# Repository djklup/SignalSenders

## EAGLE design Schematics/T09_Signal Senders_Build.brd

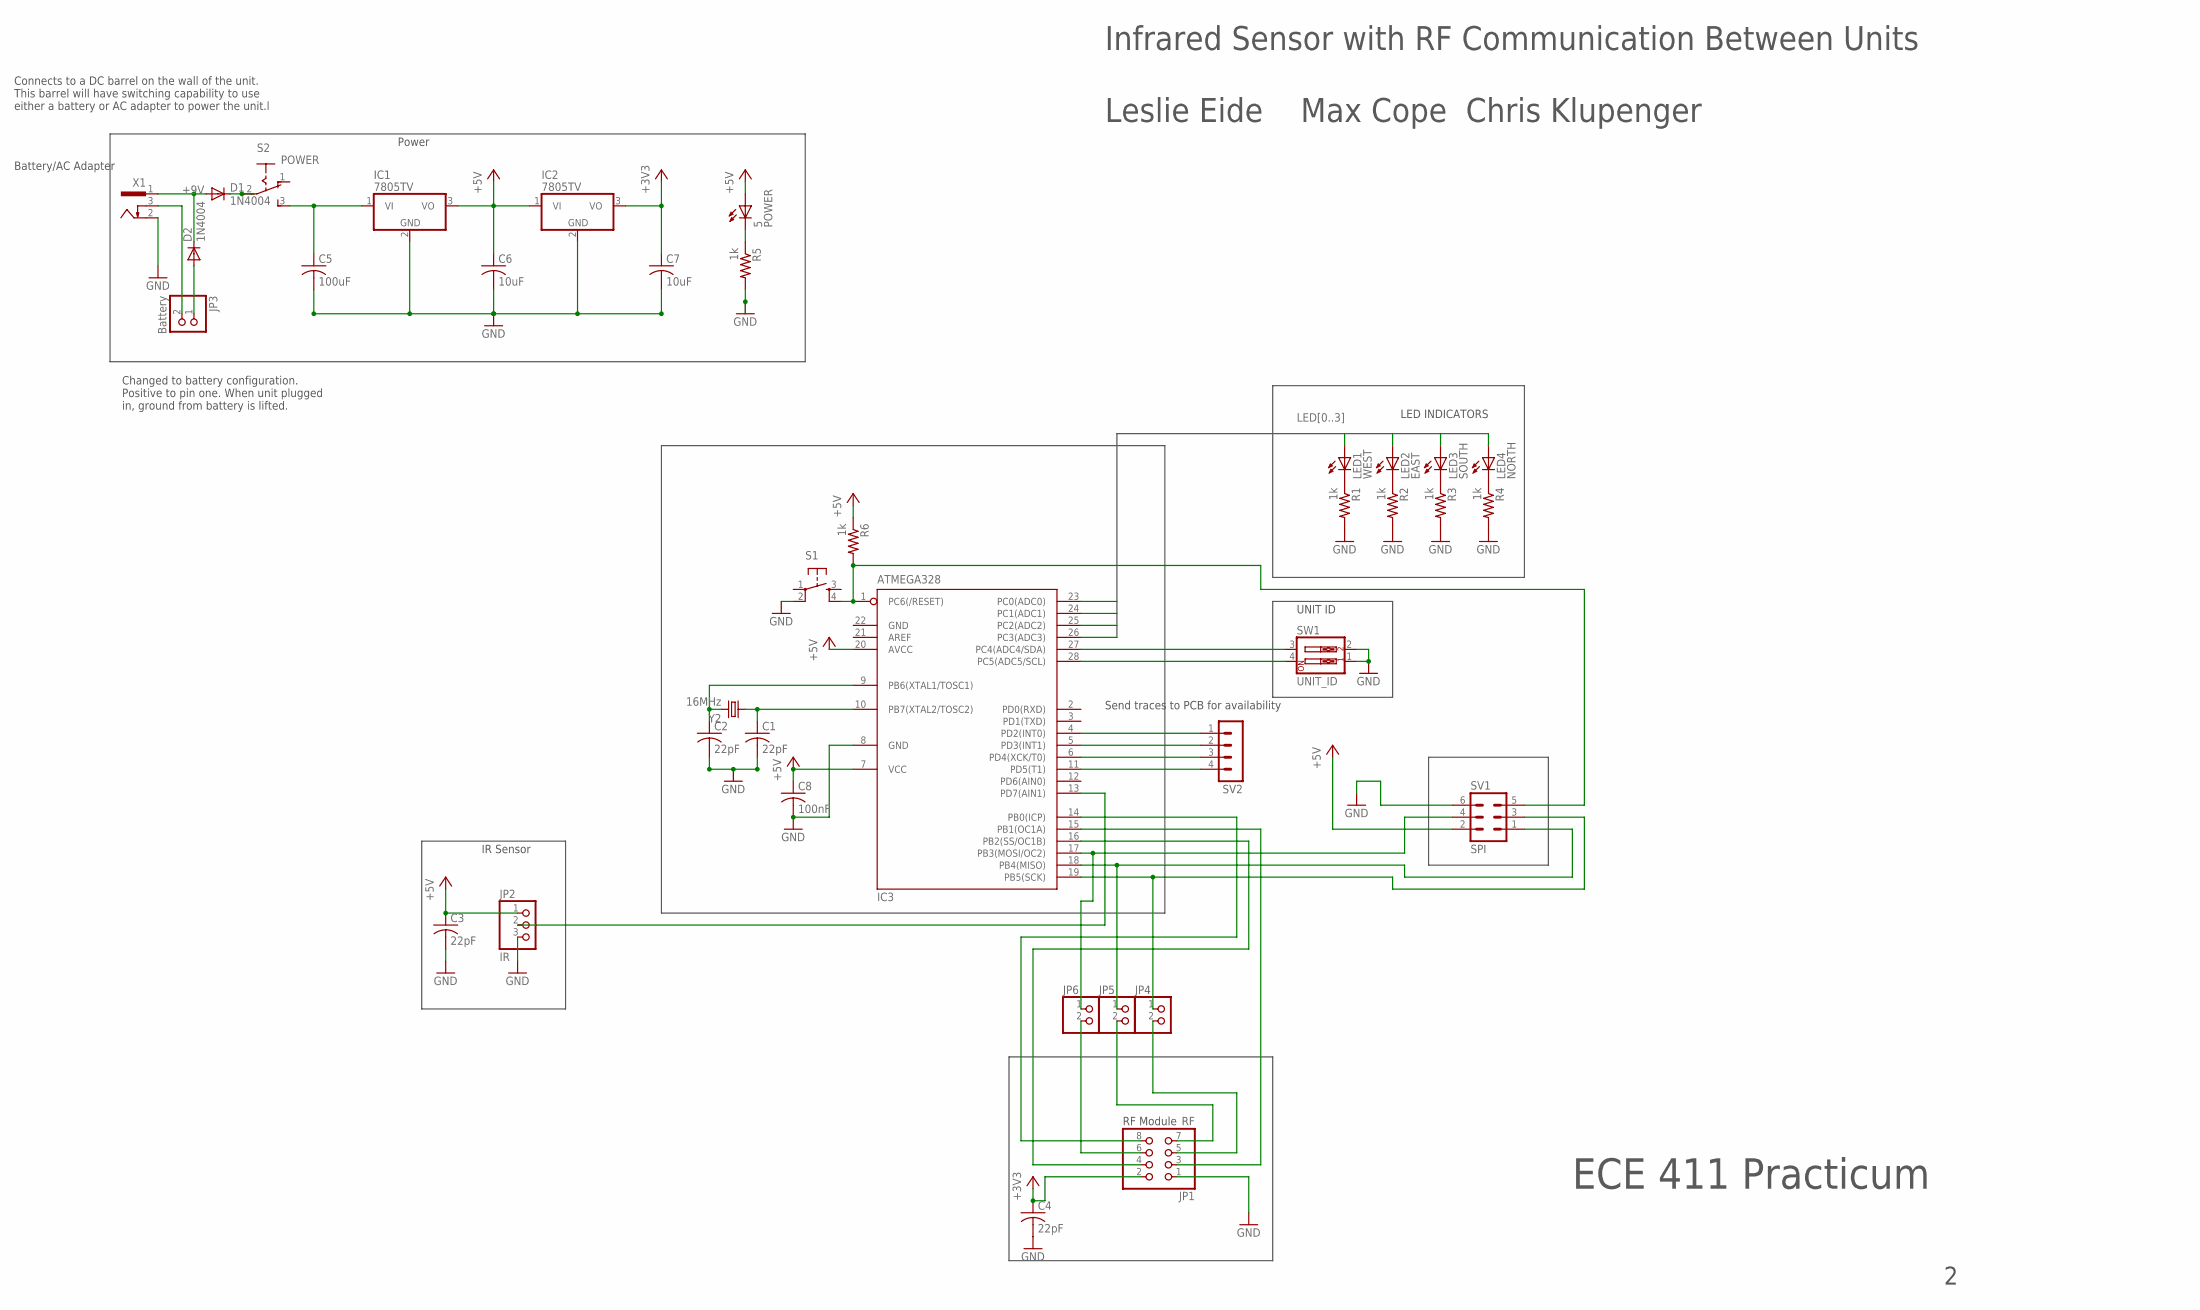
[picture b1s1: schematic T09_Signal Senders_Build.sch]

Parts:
5: POWER; LED3MM
C1, C2, C3, C4: 22pF; C0805
C5: 100uF; C050-075X075
C6, C7: 10uF; C0805
C8: 100nF; C0805
D1, D2: 1N4004; DO41-10
IC1, IC2: 7805TV; TO220V
IC3: ATMEGA328; DIL28-3
JP1: RF; 2X04
JP2: IR; 1X03
JP3: Battery; 1X02
JP4, JP5, JP6: 1X02
LED1: WEST; LED3MM
LED2: EAST; LED3MM
LED3: SOUTH; LED3MM
LED4: NORTH; LED3MM
R1, R2, R3, R4, R5, R6: 1k; M0805
S1: TACTILE-PTH
S2: POWER; M251
SV1: SPI; MA03-2
SV2: MA04-1
SW1: UNIT_ID; EDG-02
X1: 733980-62
Y2: 16MHz; HC49US

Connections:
+3V3: C4.1, C7.1, IC2.3 (VO), JP1.2
+5V: 5.A, C3.1, C6.1, C8.1, IC1.3 (VO), IC2.1 (VI), IC3.7 (VCC), IC3.20 (AVCC), JP2.1, R6.1, SV1.2
+9V: D1.A, D2.C, X1.1
GND: C1.2, C2.2, C3.2, C4.2, C5.2, C6.2, C7.2, C8.2, IC1.2 (GND), IC2.2 (GND), IC3.8 (GND), IC3.22 (GND), JP1.1, JP2.3, R1.2, R2.2, R3.2, R4.2, R5.2, S1.2, SV1.6, SW1.1, SW1.2, X1.2
LED0: IC3.23 (PC0(ADC0)), LED1.A
LED1: IC3.24 (PC1(ADC1)), LED2.A
LED2: IC3.25 (PC2(ADC2)), LED3.A
LED3: IC3.26 (PC3(ADC3)), LED4.A
unnamed: IC3.1 (PC6(/RESET)), R6.2, S1.4, SV1.5
unnamed: C1.1, IC3.10 (PB7(XTAL2/TOSC2)), Y2.1
unnamed: C2.1, IC3.9 (PB6(XTAL1/TOSC1)), Y2.2
unnamed: IC3.13 (PD7(AIN1)), JP2.2
unnamed: LED1.K (C), R1.1
unnamed: LED2.K (C), R2.1
unnamed: LED3.K (C), R3.1
unnamed: LED4.K (C), R4.1
unnamed: IC3.27 (PC4(ADC4/SDA)), SW1.3
unnamed: IC3.28 (PC5(ADC5/SCL)), SW1.4
unnamed: IC3.4 (PD2(INT0)), SV2.1
unnamed: IC3.5 (PD3(INT1)), SV2.2
unnamed: D2.A, JP3.1
unnamed: JP3.2, X1.3
unnamed: IC3.6 (PD4(XCK/T0)), SV2.3
unnamed: IC3.11 (PD5(T1)), SV2.4
unnamed: 5.K (C), R5.1
unnamed: C5.1, IC1.1 (VI), S2.3 (S)
unnamed: D1.C, S2.2
unnamed: IC3.18 (PB4(MISO)), JP5.1, SV1.1
unnamed: IC3.17 (PB3(MOSI/OC2)), JP6.1, SV1.4
unnamed: IC3.19 (PB5(SCK)), JP4.1, SV1.3
unnamed: IC3.16 (PB2(SS/OC1B)), JP1.4
unnamed: IC3.14 (PB0(ICP)), JP1.8
unnamed: IC3.15 (PB1(OC1A)), JP1.3
unnamed: JP1.6, JP6.2
unnamed: JP1.7, JP5.2
unnamed: JP1.5, JP4.2

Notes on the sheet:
LED INDICATORS
RF Module
IR Sensor
UNIT ID
Power
Infrared Sensor with RF Communication Between Units Leslie Eide Max Cope Chris Klupenger
Battery/AC Adapter
ECE 411 Practicum
Send traces to PCB for availability
Connects to a DC barrel on the wall of the unit. This barrel will have switching capability to use either a battery or AC adapter to power the unit.l
Changed to battery configuration. Positive to pin one. When unit plugged in, ground from battery is lifted.

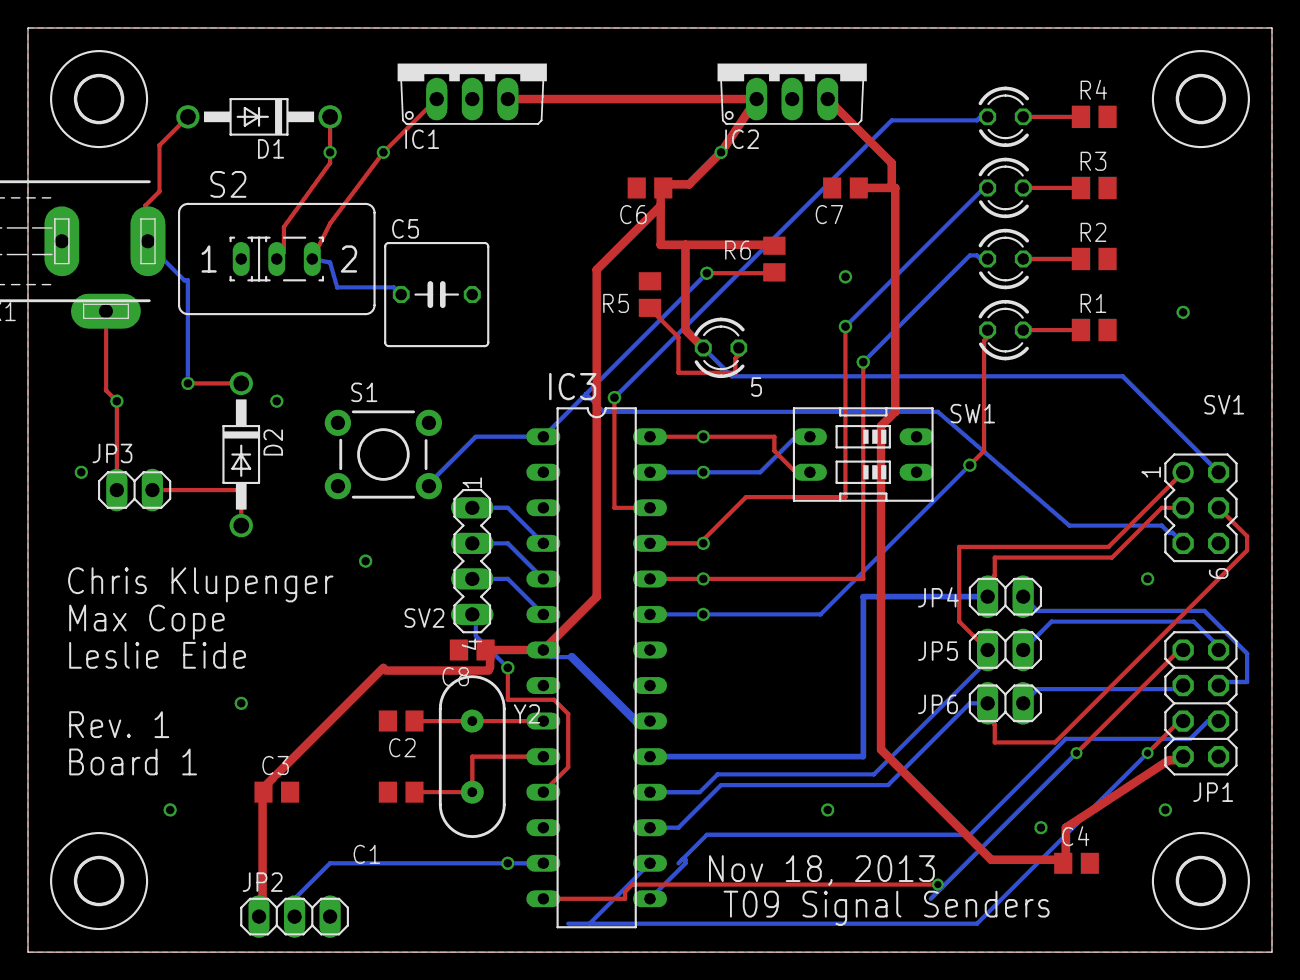
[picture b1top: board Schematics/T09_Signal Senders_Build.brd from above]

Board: 2 copper layers, 88.9 x 66.0 mm, 41 parts (0 on the bottom side), 36 nets.

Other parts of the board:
U$1, U$2, U$3, U$4: 3,2

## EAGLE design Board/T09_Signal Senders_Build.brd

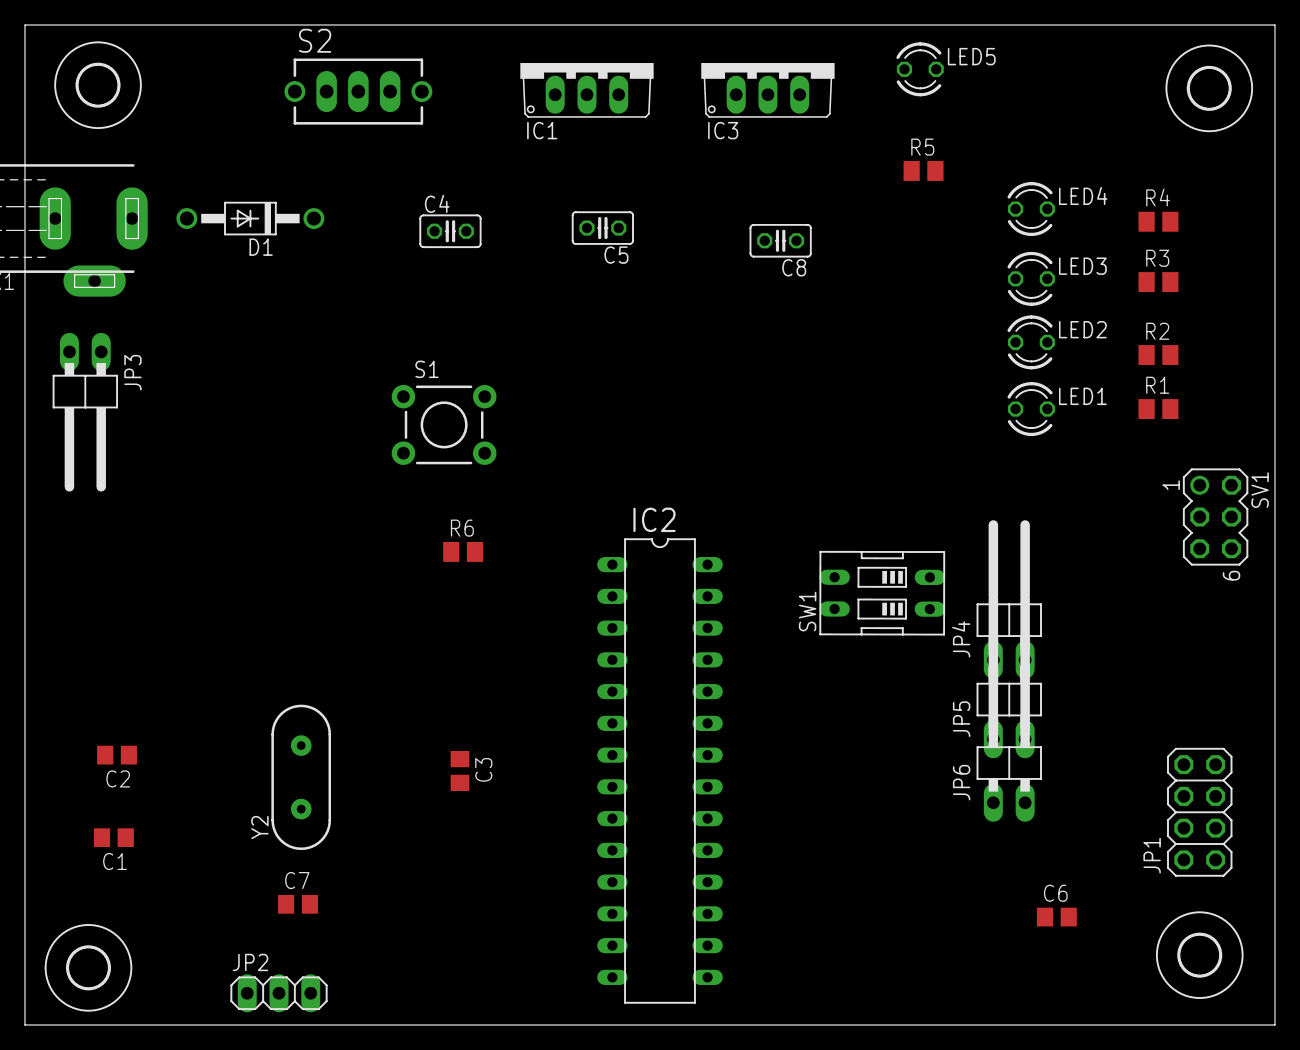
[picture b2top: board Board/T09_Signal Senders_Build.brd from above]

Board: 2 copper layers, 100.0 x 80.0 mm, 39 parts (0 on the bottom side), 28 nets, no tracks yet.

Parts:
C1, C2, C6, C7: 22pF; C0805
C3: 100nF; C0805
C4: 100u; C025-025X050
C5, C8: 10u; C025-025X050
D1: 1N4004; DO41-10
IC1, IC3: 7805TV; TO220V
IC2: ATMEGA328; DIL28-3
JP1: 2X03
JP2: 1X03
JP3, JP4, JP5, JP6: 1X02/90
LED1, LED5: RED; LED3MM
LED2: GREEN; LED3MM
LED3: YELLOW; LED3MM
LED4: BLUE; LED3MM
R1, R2, R3, R4, R5, R6: 1k; M0805
S1: TACTILE-PTH
S2: TL32YO; TL3XYO
SV1: MA03-2
SW1: EDG-02
U$1, U$2, U$3, U$4: 3,2
X1: 733980-62
Y2: 16MHz; HC49US

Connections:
+3V3: C6.1, C8.1, IC3.3, JP1.2
+5V: C3.1, C5.1, C7.1, IC1.3, IC2.7, IC2.20, IC3.1, JP2.1, LED5.A, R6.1, SV1.2
+9V: D1.A, X1.1
GND: C1.2, C2.2, C3.2, C4.2, C5.2, C6.2, C7.2, C8.2, IC1.2, IC2.8, IC2.22, IC3.2, JP1.1, JP2.3, JP3.2, R1.2, R2.2, R3.2, R4.2, R5.2, S1.2, SV1.6, SW1.1, SW1.2, X1.2
LED0: IC2.23, LED1.A
LED1: IC2.24, LED2.A
LED2: IC2.25, LED3.A
LED3: IC2.26, LED4.A
unnamed: IC2.1, R6.2, S1.4, SV1.5
unnamed: C1.1, IC2.10, Y2.1
unnamed: C2.1, IC2.9, Y2.2
unnamed: IC2.13, JP2.2
unnamed: LED1.K, R1.1
unnamed: LED2.K, R2.1
unnamed: LED3.K, R3.1
unnamed: LED4.K, R4.1
unnamed: IC2.27, SW1.3
unnamed: IC2.28, SW1.4
unnamed: JP3.1, X1.3
unnamed: LED5.K, R5.1
unnamed: C4.1, IC1.1, S2.3
unnamed: D1.C, S2.2
RF_SPI0: IC2.14, IC2.16, JP1.3, JP1.4
RF_SPI1: IC2.15, JP1.8
RF_SPI2: JP1.5, JP4.2
RF_SPI3: IC2.17, JP1.6, JP6.1, JP6.2, SV1.4
RF_SPI4: IC2.18, JP1.7, JP5.1, JP5.2, SV1.1
RF_SPI5: IC2.19, JP4.1, SV1.3

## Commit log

2013-10-22 Datasheets added
2013-10-22 Create datasheet folder
2013-10-22 add microprocessor flowchart
2013-10-22 added parts receipt for 3 ATMEGA microprocessors
2013-10-23 Add PDS document first draft
2013-10-30 Initial Timeline
2013-11-04 Update 11/4
2013-11-04 First Eagle draft
2013-11-04 changed crystal oscillator
    changed crystal oscillator to COM-00536
2013-11-04 add reset switch, add power input capacitor
2013-11-04 untied the lines from chip to LEDs
2013-11-05 EAGLE - upated RF module to 2x4
2013-11-05 EAGLE - add headers for Tx and Rx
    Headers to be able to easily program the chip
2013-11-05 Eagle Schematic - Max's changes to draft to turn in
    first draft being turned in to Andrew of Eagle schematic
2013-11-06 Updated Schematic
    Changed Border. Added wires to open uC I/O.
2013-11-06 Cleaned repo.
    Reorganized files.
2013-11-06 Created Spreadsheet
2013-11-06 Created BOM
2013-11-06 Updated Status. Added layout to action items.
2013-11-07 Added 3.3V Rail. Can use panel mounted DC barrel.
2013-11-07 Changed Part.
2013-11-08 first draft
2013-11-08 Updated project
2013-11-09 Modified SPI section. Added DC barrel.
2013-11-09 Added part verification needed for schematic.
2013-11-09 add 6 pin header for programming
2013-11-09 Fixed many ERC errors
2013-11-11 first draft PCB layout
    first placements of components on PCB layout - no routing of traces has
    been done
2013-11-12 Created PCB Diagram
2013-11-12 Moved to New Folder
2013-11-12 Moved Board Layout to Separate Folder
2013-11-12 Still Building
2013-11-12 Rearranged Battery Configuration. Still an Issue with RF SPI Nets
2013-11-13 new board layout
    smaller size, updated components, etc.
2013-11-13 new board layout
    updated stuff
2013-11-13 Routed all the signals on the PCB
2013-11-13 Final Project Timeline
2013-11-14 PCB - added vias, added headers to uC unused pins
2013-11-16 Fixed Nets. Fixed Silkscreen Layer
2013-11-16 Added Components
2013-11-17 RF nets still had errors. Still need to be routed.
2013-11-17 Finished all but power switch.
    Need to find a footprint that will match what we can buy.
2013-11-17 Minor changes to traces.
2013-11-18 Routed traces to PCB
2013-11-18 routed traces to PCB
    last commit didn't seem to work
2013-11-18 Updated Board
2013-11-18 Andrew's fixes from office hours
2013-11-19 Fixes as per Andrews recommendations
    vcc lines larger, gnd vias, move crystal and bypass caps, add diode to
    battery, version, names
2013-11-19 Changed RF_SPI Pinout
2013-11-19 Routed 3 last pins to SPI RF
2013-11-20 Completed Order
2013-11-20 Added details for modules, pcb, and housing.
2013-11-21 Initial Testing Plan and System Design
2013-11-25 Filled in some Testing Plan
2013-11-27 Add pdf file of schematic
2013-11-27 add pdf file of schmatic
2013-11-27 Updated Testing Plan
    Missing data where lkfjslthe lies.
2013-11-27 Added RF Tests. Still need to finish one.
2013-11-27 Modified. Still needs data sheets but added model numbers.
2013-11-27 PDS Updated
2013-11-27 update A lot of stuff
2013-11-27 commit
    commit
2013-12-01 Updated Presentation
2013-12-02 Added a few pictures. Modified some aesthetics.
2013-12-02 Updated colors
2013-12-03 add schematic to powerpoint
2013-12-03 add border to schematic on powerpoint
2013-12-03 recommit
2013-12-03 Review 3
2013-12-03 Presentation for Faust
2013-12-03 Added Content
2013-12-03 Interaction model on powerpoint.
2013-12-04 Powerpoint - add slides
    Implementation Power schematic, modules schematic, PCB,
    Verification slide
2013-12-07 initial firmware
    initial firmware
2013-12-07 turn on 4 leds
2013-12-07 added in timer
2013-12-07 testing complete
    works 100% as desired with 2 units fully tested - need to test with 3
    and 4 units now.
2013-12-09 add start up light sequence
2013-12-11 add code for demo board
    add code for demo board (untested)
2013-12-13 Updated Aesthetics
2013-12-13 Final Presentation and updated SDM to revision 2
2013-12-16 pictures and movies
2013-12-19 changed PDS to new update

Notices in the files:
parts and their libraries:
SparkFun-Electromechanical: Licensing: CC v3.0 Share-Alike You are welcome to use this library for commercial purposes.
